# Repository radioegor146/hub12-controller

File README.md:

# hub12-controller

Simple HUB12 LED matrices USB controller using RP2040
Currently it is ready to use for 224x192 (7x12) 32x16 monochrome (red) matrices 
It uses:
- PIO to control 12 simultaneous SPI lanes
- DMA to push data to PIO
- Low-level USB w/o any libraries to push data to buffer

It achieves:
- ~160 FPS on 224x192 monochrome display with 12 parallel lanes

Pins are set in [this file](src/hub12.h)

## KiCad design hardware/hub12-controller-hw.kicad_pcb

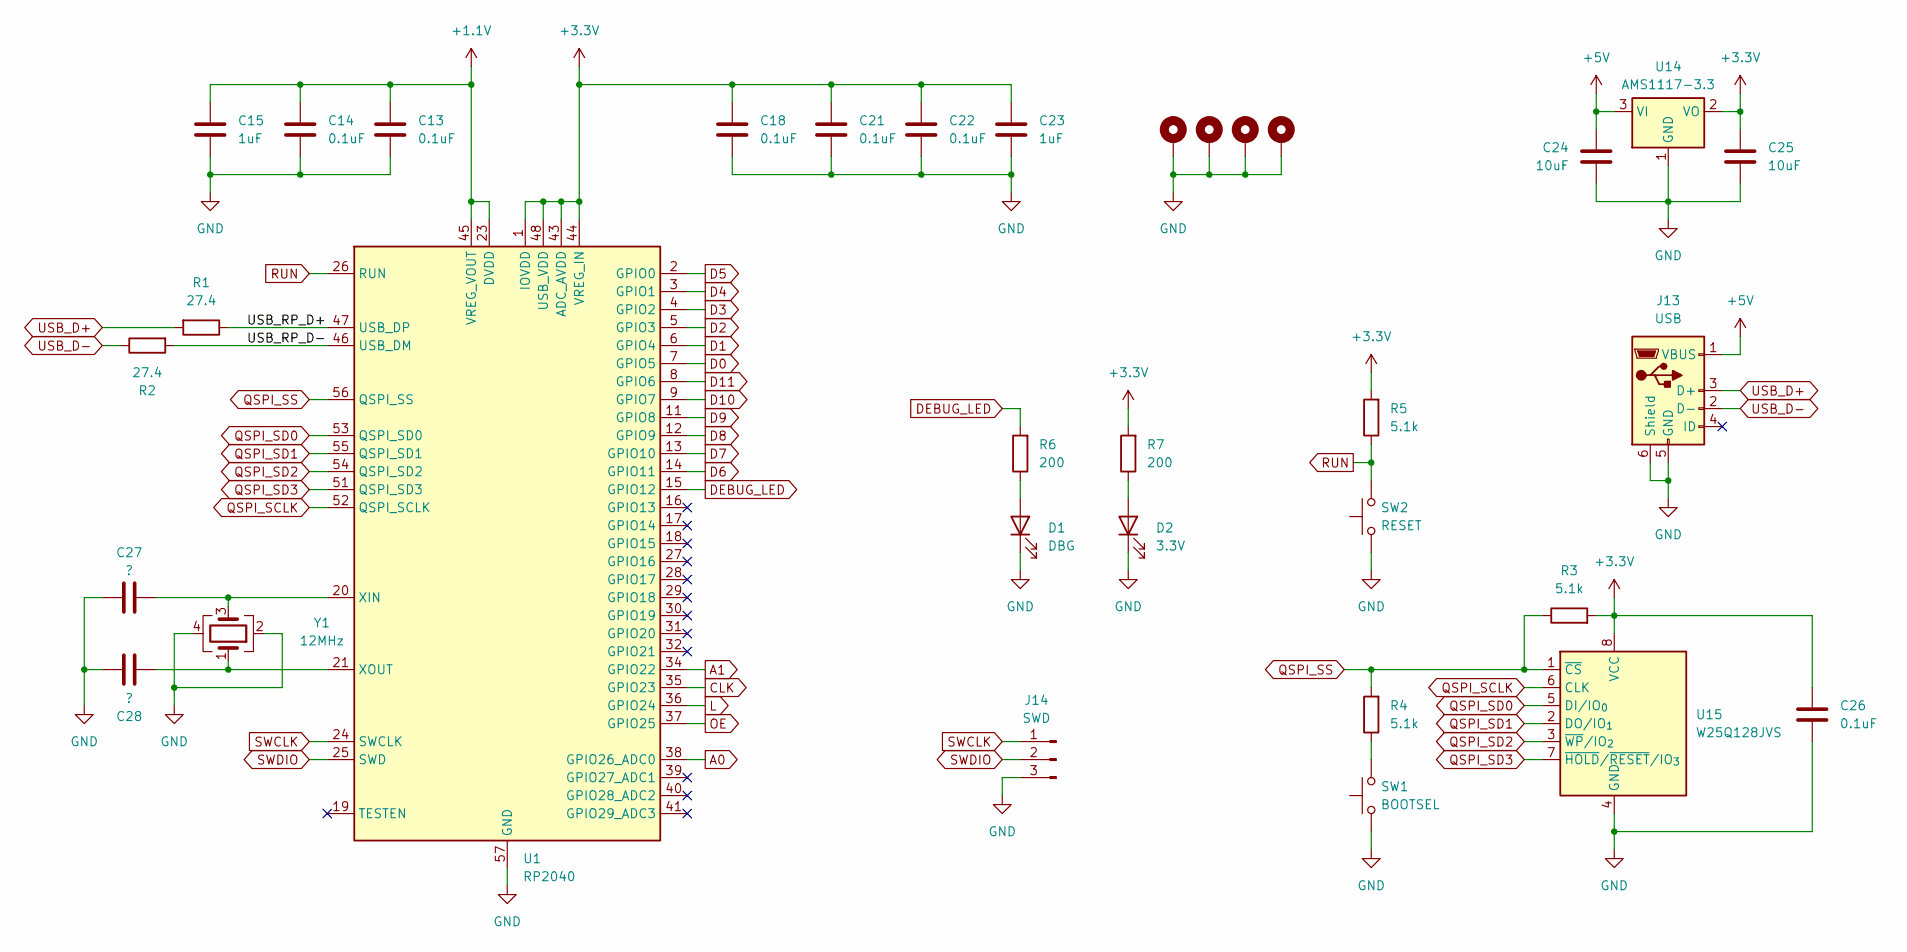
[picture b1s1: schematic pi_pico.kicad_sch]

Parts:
C13, C14, C18, C21, C22, C26: 0.1uF; C_0805_2012Metric
C15, C23: 1uF; C_0805_2012Metric
C24, C25: 10uF; C_0805_2012Metric
C27, C28: ?; C_0805_2012Metric
D1: DBG; LED_0805_2012Metric
D2: 3.3V; LED_0805_2012Metric
H1, H2, H3, H4: MountingHole_3.2mm_M3_DIN965_Pad_TopBottom
J13: USB; USB_Mini-B_Wuerth_65100516121_Horizontal
J14: SWD; PinHeader_1x03_P2.54mm_Vertical
R1, R2: 27.4; R_0805_2012Metric
R3, R4, R5: 5.1k; R_0805_2012Metric
R6, R7: 200; R_0805_2012Metric
SW1: BOOTSEL; SW_Push_SPST_NO_Alps_SKRK
SW2: RESET; SW_Push_SPST_NO_Alps_SKRK
U1: RP2040; QFN-56-1EP_7x7mm_P0.4mm_EP3.2x3.2mm
U14: AMS1117-3.3; SOT-223-3_TabPin2
U15: W25Q128JVS; SOIC-8_5.3x5.3mm_P1.27mm
Y1: 12MHz; Crystal_SMD_3225-4Pin_3.2x2.5mm_HandSoldering

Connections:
+1.1V: C13.1, C14.1, C15.1, U1.23 (DVDD), U1.45 (VREG_VOUT), U1.50 (DVDD)
+3.3V: C18.1, C21.1, C22.1, C23.1, C25.1, C26.1, R3.2, R5.2, R7.2, U1.1 (IOVDD), U1.10 (IOVDD), U1.22 (IOVDD), U1.33 (IOVDD), U1.42 (IOVDD), U1.43 (ADC_AVDD), U1.44 (VREG_IN), U1.48 (USB_VDD), U1.49 (IOVDD), U14.2 (VO), U15.8 (VCC); also elsewhere on the board
+5V: C24.1, J13.1 (VBUS), U14.3 (VI); also elsewhere on the board
/Pi Pico/USB_RP_D+: R1.1, U1.47 (USB_DP)
/Pi Pico/USB_RP_D-: R2.2, U1.46 (USB_DM)
A0: U1.38 (GPIO26_ADC0); also elsewhere on the board
A1: U1.34 (GPIO22); also elsewhere on the board
CLK: U1.35 (GPIO23); also elsewhere on the board
D0: U1.7 (GPIO5); also elsewhere on the board
D1: U1.6 (GPIO4); also elsewhere on the board
D2: U1.5 (GPIO3); also elsewhere on the board
D3: U1.4 (GPIO2); also elsewhere on the board
D4: U1.3 (GPIO1); also elsewhere on the board
D5: U1.2 (GPIO0); also elsewhere on the board
D6: U1.14 (GPIO11); also elsewhere on the board
D7: U1.13 (GPIO10); also elsewhere on the board
D8: U1.12 (GPIO9); also elsewhere on the board
D9: U1.11 (GPIO8); also elsewhere on the board
D10: U1.9 (GPIO7); also elsewhere on the board
D11: U1.8 (GPIO6); also elsewhere on the board
DEBUG_LED: R6.2, U1.15 (GPIO12)
GND: C13.2, C14.2, C15.2, C18.2, C21.2, C22.2, C23.2, C24.2, C25.2, C26.2, C27.1, C28.2, D1.1 (K), D2.1 (K), H1.1, H2.1, H3.1, H4.1, J13.5 (GND), J13.6 (Shield), J14.3, SW1.1, SW2.1, U1.57 (GND), U14.1 (GND), U15.4 (GND), Y1.2, Y1.4; also elsewhere on the board
L: U1.36 (GPIO24); also elsewhere on the board
unnamed: D1.2 (A), R6.1
unnamed: D2.2 (A), R7.1
unnamed: R4.1, SW1.2
unnamed: C27.2, U1.20 (XIN), Y1.3
unnamed: C28.1, U1.21 (XOUT), Y1.1
OE: U1.37 (GPIO25); also elsewhere on the board
QSPI_SCLK: U1.52 (QSPI_SCLK), U15.6 (CLK)
QSPI_SD0: U1.53 (QSPI_SD0), U15.5 (DI/IO_{0})
QSPI_SD1: U1.55 (QSPI_SD1), U15.2 (DO/IO_{1})
QSPI_SD2: U1.54 (QSPI_SD2), U15.3 (~WP/IO_{2})
QSPI_SD3: U1.51 (QSPI_SD3), U15.7 (~HOLD/~RESET/IO_{3})
QSPI_SS: R3.1, R4.2, U1.56 (QSPI_SS), U15.1 (~CS)
RUN: R5.1, SW2.2, U1.26 (RUN)
SWCLK: J14.1, U1.24 (SWCLK)
SWDIO: J14.2, U1.25 (SWD)
USB_D+: J13.3 (D+), R1.2
USB_D-: J13.2 (D-), R2.1

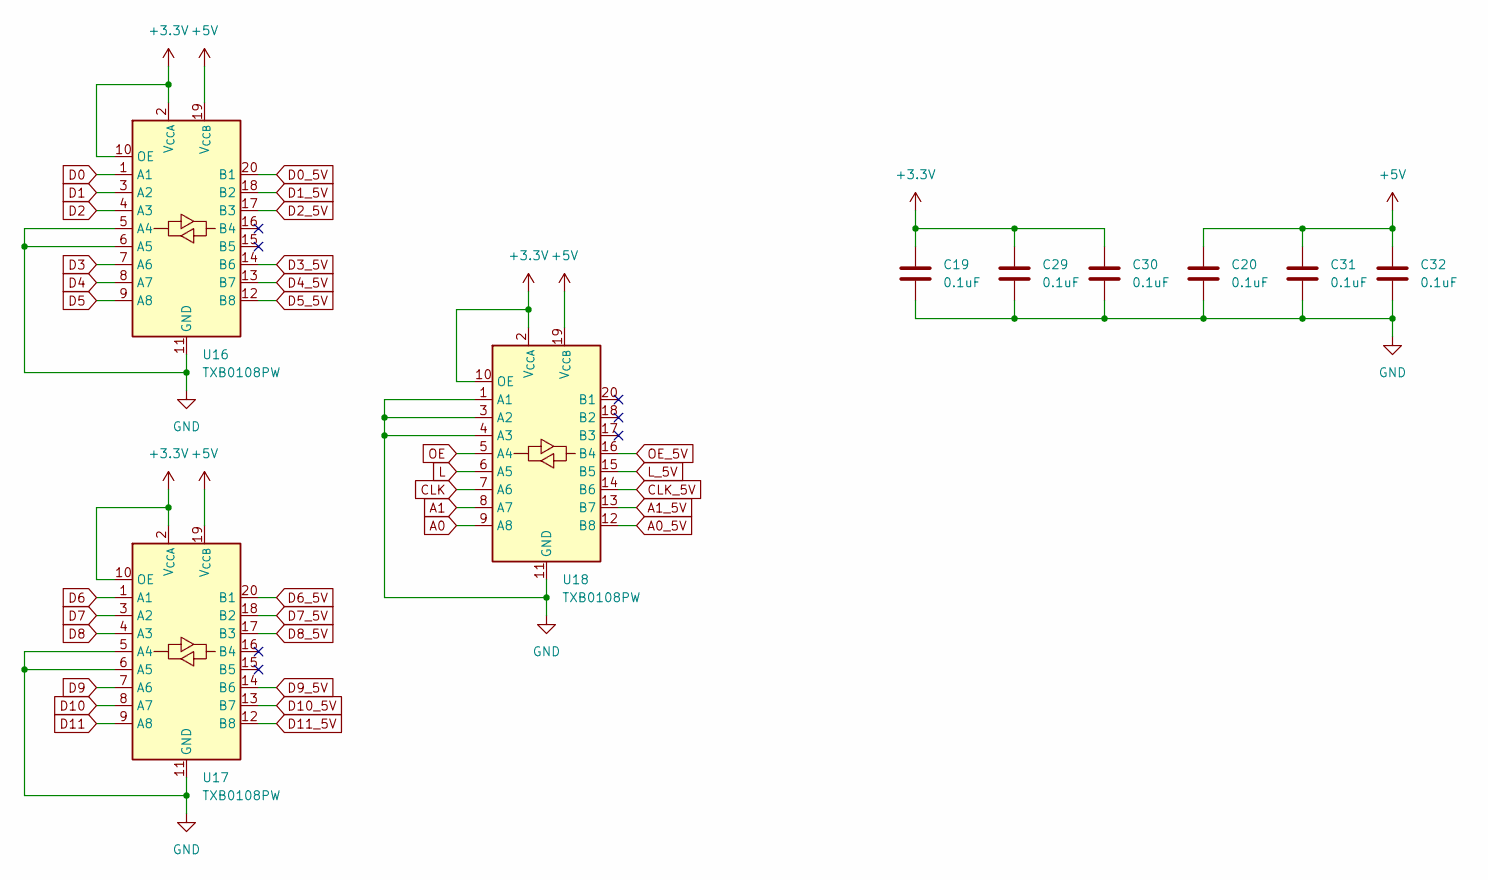
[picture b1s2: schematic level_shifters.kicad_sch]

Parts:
C19, C20, C29, C30, C31, C32: 0.1uF; C_0805_2012Metric
U16, U17, U18: TXB0108PW; TSSOP-20_4.4x6.5mm_P0.65mm

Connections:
+3.3V: C19.1, C29.1, C30.1, U16.2 (V_{CCA}), U16.10 (OE), U17.2 (V_{CCA}), U17.10 (OE), U18.2 (V_{CCA}), U18.10 (OE); also elsewhere on the board
+5V: C20.1, C31.1, C32.1, U16.19 (V_{CCB}), U17.19 (V_{CCB}), U18.19 (V_{CCB}); also elsewhere on the board
A0: U18.9 (A8); also elsewhere on the board
A0_5V: U18.12 (B8); also elsewhere on the board
A1: U18.8 (A7); also elsewhere on the board
A1_5V: U18.13 (B7); also elsewhere on the board
CLK: U18.7 (A6); also elsewhere on the board
CLK_5V: U18.14 (B6); also elsewhere on the board
D0: U16.1 (A1); also elsewhere on the board
D0_5V: U16.20 (B1); also elsewhere on the board
D1: U16.3 (A2); also elsewhere on the board
D1_5V: U16.18 (B2); also elsewhere on the board
D2: U16.4 (A3); also elsewhere on the board
D2_5V: U16.17 (B3); also elsewhere on the board
D3: U16.7 (A6); also elsewhere on the board
D3_5V: U16.14 (B6); also elsewhere on the board
D4: U16.8 (A7); also elsewhere on the board
D4_5V: U16.13 (B7); also elsewhere on the board
D5: U16.9 (A8); also elsewhere on the board
D5_5V: U16.12 (B8); also elsewhere on the board
D6: U17.1 (A1); also elsewhere on the board
D6_5V: U17.20 (B1); also elsewhere on the board
D7: U17.3 (A2); also elsewhere on the board
D7_5V: U17.18 (B2); also elsewhere on the board
D8: U17.4 (A3); also elsewhere on the board
D8_5V: U17.17 (B3); also elsewhere on the board
D9: U17.7 (A6); also elsewhere on the board
D9_5V: U17.14 (B6); also elsewhere on the board
D10: U17.8 (A7); also elsewhere on the board
D10_5V: U17.13 (B7); also elsewhere on the board
D11: U17.9 (A8); also elsewhere on the board
D11_5V: U17.12 (B8); also elsewhere on the board
GND: C19.2, C20.2, C29.2, C30.2, C31.2, C32.2, U16.5 (A4), U16.6 (A5), U16.11 (GND), U17.5 (A4), U17.6 (A5), U17.11 (GND), U18.1 (A1), U18.3 (A2), U18.4 (A3), U18.11 (GND); also elsewhere on the board
L: U18.6 (A5); also elsewhere on the board
L_5V: U18.15 (B5); also elsewhere on the board
OE: U18.5 (A4); also elsewhere on the board
OE_5V: U18.16 (B4); also elsewhere on the board

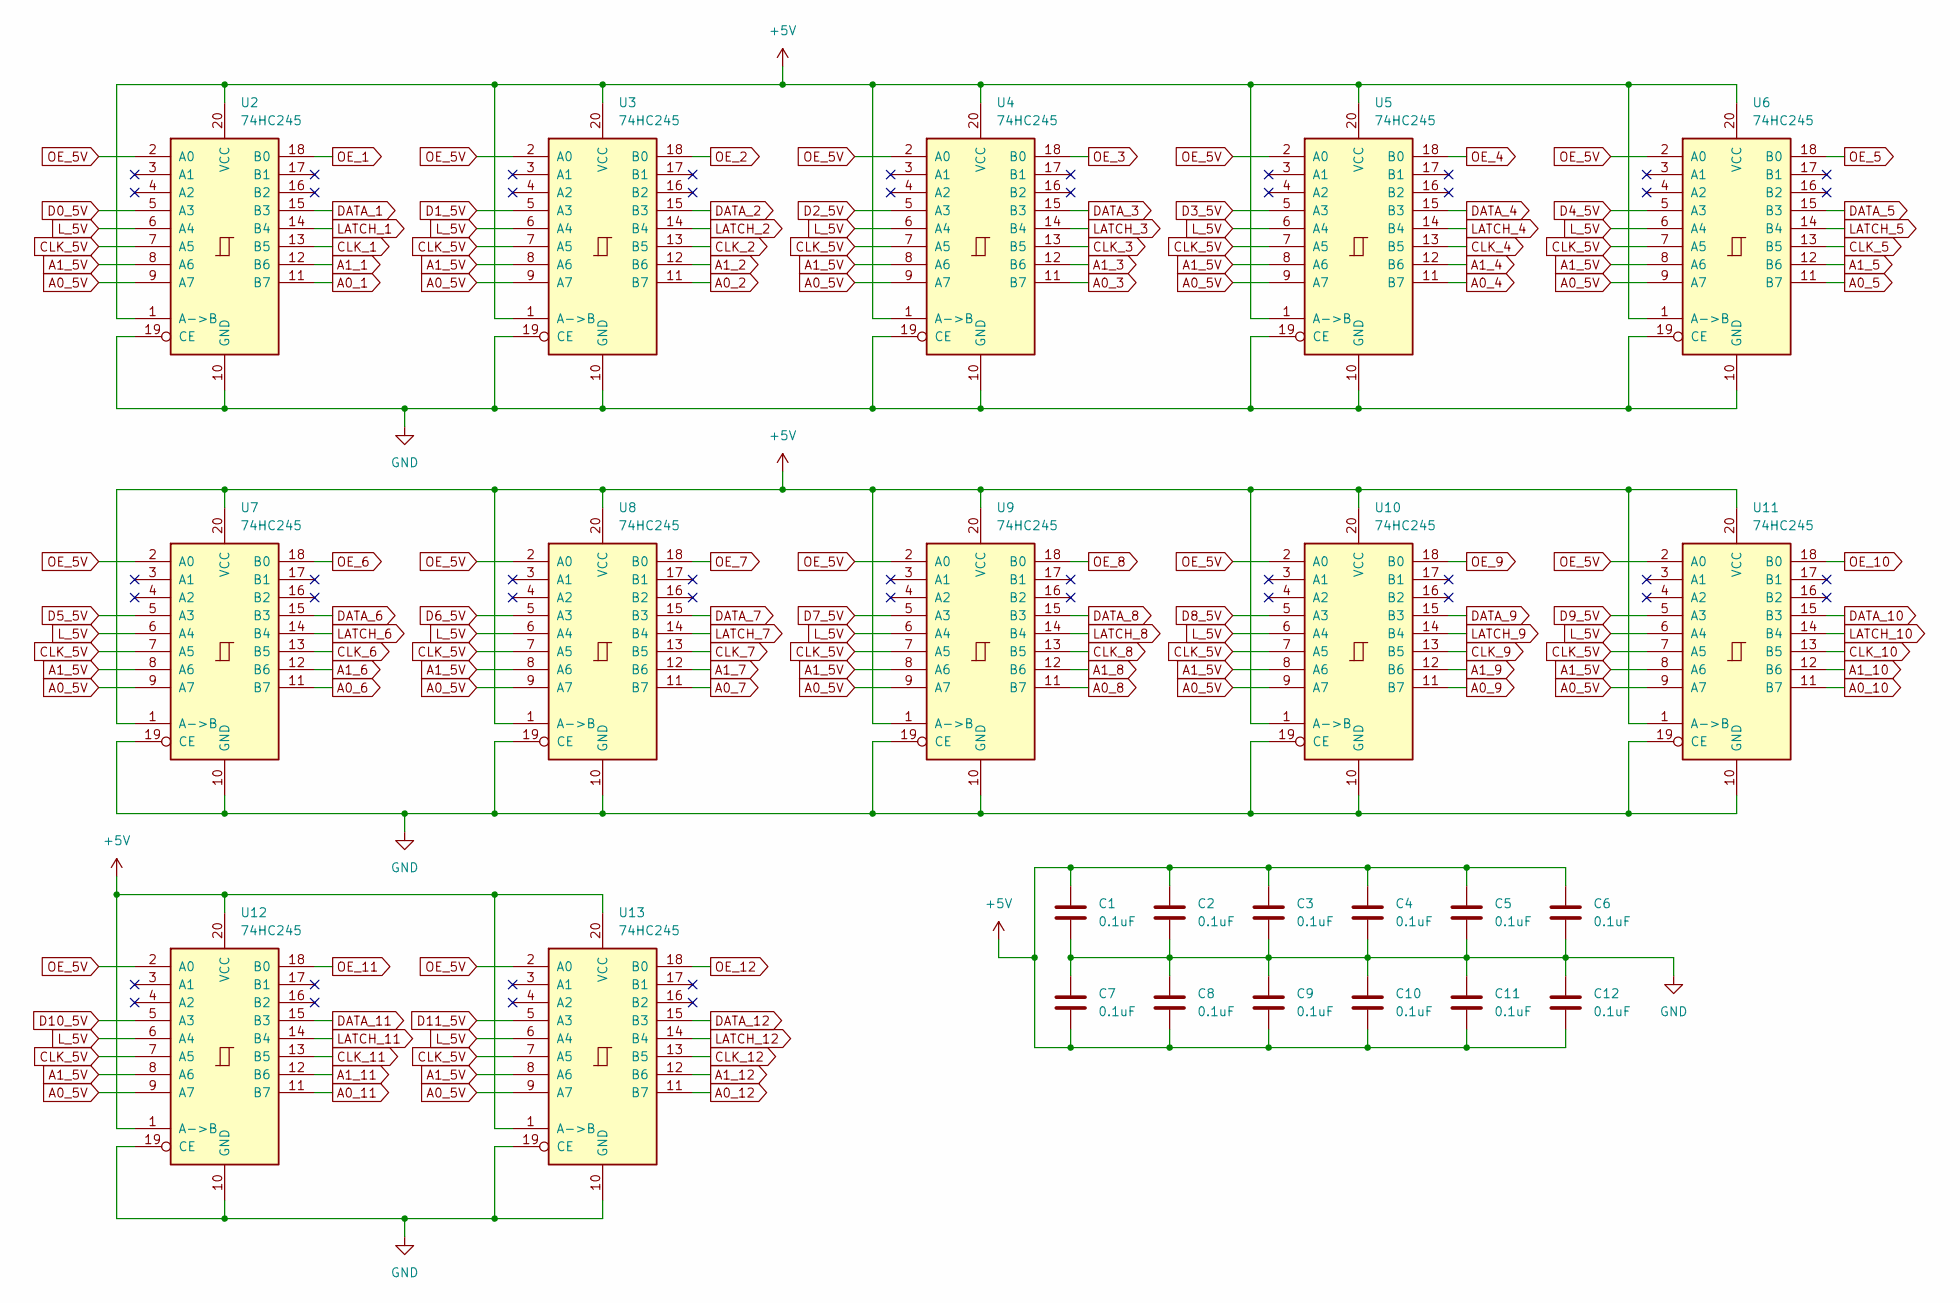
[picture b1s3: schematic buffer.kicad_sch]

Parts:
C1, C2, C3, C4, C5, C6, C7, C8, C9, C10, C11, C12: 0.1uF; C_0805_2012Metric
U2, U3, U4, U5, U6, U7, U8, U9, U10, U11, U12, U13: 74HC245; TSSOP-20_4.4x6.5mm_P0.65mm

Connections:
+5V: C1.1, C2.1, C3.1, C4.1, C5.1, C6.1, C7.2, C8.2, C9.2, C10.2, C11.2, C12.2, U2.1 (A->B), U2.20 (VCC), U3.1 (A->B), U3.20 (VCC), U4.1 (A->B), U4.20 (VCC), U5.1 (A->B), U5.20 (VCC), U6.1 (A->B), U6.20 (VCC), U7.1 (A->B), U7.20 (VCC), U8.1 (A->B), U8.20 (VCC), U9.1 (A->B), U9.20 (VCC), U10.1 (A->B), U10.20 (VCC), U11.1 (A->B), U11.20 (VCC), U12.1 (A->B), U12.20 (VCC), U13.1 (A->B), U13.20 (VCC); also elsewhere on the board
A0_1: U2.11 (B7); also elsewhere on the board
A0_2: U3.11 (B7); also elsewhere on the board
A0_3: U4.11 (B7); also elsewhere on the board
A0_4: U5.11 (B7); also elsewhere on the board
A0_5: U6.11 (B7); also elsewhere on the board
A0_5V: U2.9 (A7), U3.9 (A7), U4.9 (A7), U5.9 (A7), U6.9 (A7), U7.9 (A7), U8.9 (A7), U9.9 (A7), U10.9 (A7), U11.9 (A7), U12.9 (A7), U13.9 (A7); also elsewhere on the board
A0_6: U7.11 (B7); also elsewhere on the board
A0_7: U8.11 (B7); also elsewhere on the board
A0_8: U9.11 (B7); also elsewhere on the board
A0_9: U10.11 (B7); also elsewhere on the board
A0_10: U11.11 (B7); also elsewhere on the board
A0_11: U12.11 (B7); also elsewhere on the board
A0_12: U13.11 (B7); also elsewhere on the board
A1_1: U2.12 (B6); also elsewhere on the board
A1_2: U3.12 (B6); also elsewhere on the board
A1_3: U4.12 (B6); also elsewhere on the board
A1_4: U5.12 (B6); also elsewhere on the board
A1_5: U6.12 (B6); also elsewhere on the board
A1_5V: U2.8 (A6), U3.8 (A6), U4.8 (A6), U5.8 (A6), U6.8 (A6), U7.8 (A6), U8.8 (A6), U9.8 (A6), U10.8 (A6), U11.8 (A6), U12.8 (A6), U13.8 (A6); also elsewhere on the board
A1_6: U7.12 (B6); also elsewhere on the board
A1_7: U8.12 (B6); also elsewhere on the board
A1_8: U9.12 (B6); also elsewhere on the board
A1_9: U10.12 (B6); also elsewhere on the board
A1_10: U11.12 (B6); also elsewhere on the board
A1_11: U12.12 (B6); also elsewhere on the board
A1_12: U13.12 (B6); also elsewhere on the board
CLK_1: U2.13 (B5); also elsewhere on the board
CLK_2: U3.13 (B5); also elsewhere on the board
CLK_3: U4.13 (B5); also elsewhere on the board
CLK_4: U5.13 (B5); also elsewhere on the board
CLK_5: U6.13 (B5); also elsewhere on the board
CLK_5V: U2.7 (A5), U3.7 (A5), U4.7 (A5), U5.7 (A5), U6.7 (A5), U7.7 (A5), U8.7 (A5), U9.7 (A5), U10.7 (A5), U11.7 (A5), U12.7 (A5), U13.7 (A5); also elsewhere on the board
CLK_6: U7.13 (B5); also elsewhere on the board
CLK_7: U8.13 (B5); also elsewhere on the board
CLK_8: U9.13 (B5); also elsewhere on the board
CLK_9: U10.13 (B5); also elsewhere on the board
CLK_10: U11.13 (B5); also elsewhere on the board
CLK_11: U12.13 (B5); also elsewhere on the board
CLK_12: U13.13 (B5); also elsewhere on the board
D0_5V: U2.5 (A3); also elsewhere on the board
D1_5V: U3.5 (A3); also elsewhere on the board
D2_5V: U4.5 (A3); also elsewhere on the board
D3_5V: U5.5 (A3); also elsewhere on the board
D4_5V: U6.5 (A3); also elsewhere on the board
D5_5V: U7.5 (A3); also elsewhere on the board
D6_5V: U8.5 (A3); also elsewhere on the board
D7_5V: U9.5 (A3); also elsewhere on the board
D8_5V: U10.5 (A3); also elsewhere on the board
D9_5V: U11.5 (A3); also elsewhere on the board
D10_5V: U12.5 (A3); also elsewhere on the board
D11_5V: U13.5 (A3); also elsewhere on the board
DATA_1: U2.15 (B3); also elsewhere on the board
DATA_2: U3.15 (B3); also elsewhere on the board
DATA_3: U4.15 (B3); also elsewhere on the board
DATA_4: U5.15 (B3); also elsewhere on the board
DATA_5: U6.15 (B3); also elsewhere on the board
DATA_6: U7.15 (B3); also elsewhere on the board
DATA_7: U8.15 (B3); also elsewhere on the board
DATA_8: U9.15 (B3); also elsewhere on the board
DATA_9: U10.15 (B3); also elsewhere on the board
DATA_10: U11.15 (B3); also elsewhere on the board
DATA_11: U12.15 (B3); also elsewhere on the board
DATA_12: U13.15 (B3); also elsewhere on the board
GND: C1.2, C2.2, C3.2, C4.2, C5.2, C6.2, C7.1, C8.1, C9.1, C10.1, C11.1, C12.1, U2.10 (GND), U2.19 (CE), U3.10 (GND), U3.19 (CE), U4.10 (GND), U4.19 (CE), U5.10 (GND), U5.19 (CE), U6.10 (GND), U6.19 (CE), U7.10 (GND), U7.19 (CE), U8.10 (GND), U8.19 (CE), U9.10 (GND), U9.19 (CE), U10.10 (GND), U10.19 (CE), U11.10 (GND), U11.19 (CE), U12.10 (GND), U12.19 (CE), U13.10 (GND), U13.19 (CE); also elsewhere on the board
LATCH_1: U2.14 (B4); also elsewhere on the board
LATCH_2: U3.14 (B4); also elsewhere on the board
LATCH_3: U4.14 (B4); also elsewhere on the board
LATCH_4: U5.14 (B4); also elsewhere on the board
LATCH_5: U6.14 (B4); also elsewhere on the board
LATCH_6: U7.14 (B4); also elsewhere on the board
LATCH_7: U8.14 (B4); also elsewhere on the board
LATCH_8: U9.14 (B4); also elsewhere on the board
LATCH_9: U10.14 (B4); also elsewhere on the board
LATCH_10: U11.14 (B4); also elsewhere on the board
LATCH_11: U12.14 (B4); also elsewhere on the board
LATCH_12: U13.14 (B4); also elsewhere on the board
L_5V: U2.6 (A4), U3.6 (A4), U4.6 (A4), U5.6 (A4), U6.6 (A4), U7.6 (A4), U8.6 (A4), U9.6 (A4), U10.6 (A4), U11.6 (A4), U12.6 (A4), U13.6 (A4); also elsewhere on the board
OE_1: U2.18 (B0); also elsewhere on the board
OE_2: U3.18 (B0); also elsewhere on the board
OE_3: U4.18 (B0); also elsewhere on the board
OE_4: U5.18 (B0); also elsewhere on the board
OE_5: U6.18 (B0); also elsewhere on the board
OE_5V: U2.2 (A0), U3.2 (A0), U4.2 (A0), U5.2 (A0), U6.2 (A0), U7.2 (A0), U8.2 (A0), U9.2 (A0), U10.2 (A0), U11.2 (A0), U12.2 (A0), U13.2 (A0); also elsewhere on the board
OE_6: U7.18 (B0); also elsewhere on the board
OE_7: U8.18 (B0); also elsewhere on the board
OE_8: U9.18 (B0); also elsewhere on the board
OE_9: U10.18 (B0); also elsewhere on the board
OE_10: U11.18 (B0); also elsewhere on the board
OE_11: U12.18 (B0); also elsewhere on the board
OE_12: U13.18 (B0); also elsewhere on the board

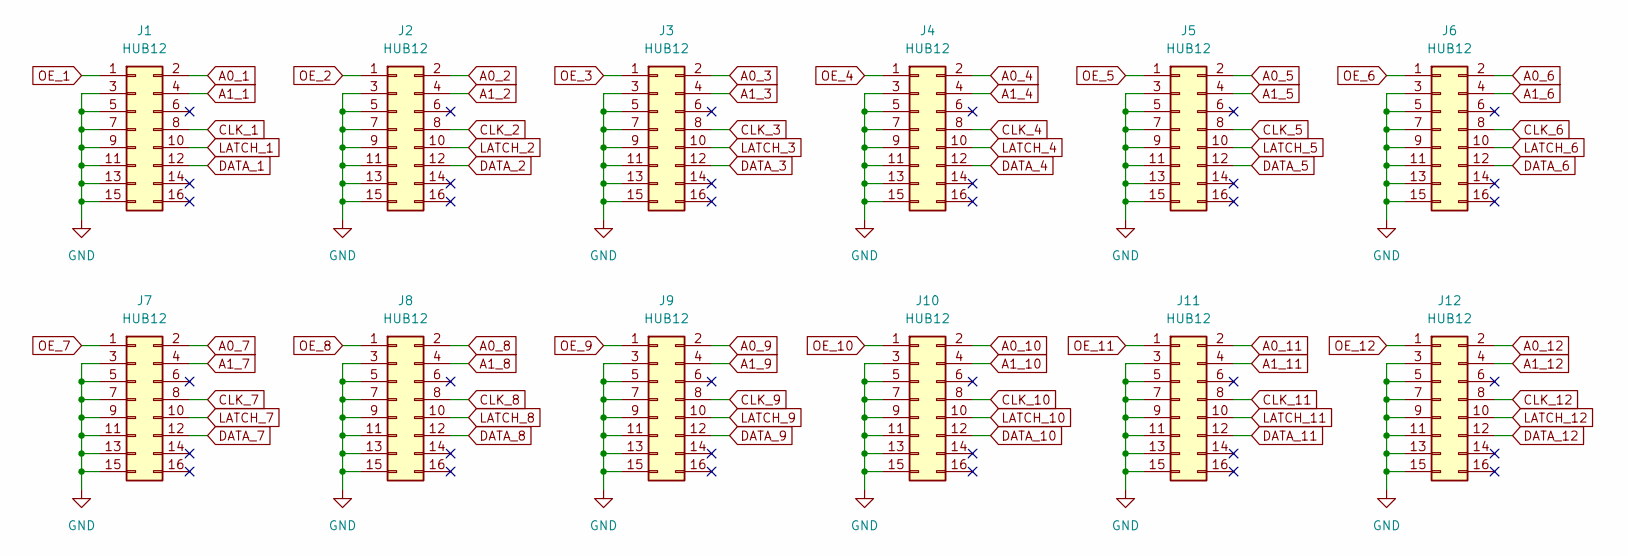
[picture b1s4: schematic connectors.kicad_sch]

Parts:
J1, J2, J3, J4, J5, J6, J7, J8, J9, J10, J11, J12: HUB12; IDC-Header_2x08_P2.54mm_Vertical

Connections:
A0_1: J1.2; also elsewhere on the board
A0_2: J2.2; also elsewhere on the board
A0_3: J3.2; also elsewhere on the board
A0_4: J4.2; also elsewhere on the board
A0_5: J5.2; also elsewhere on the board
A0_6: J6.2; also elsewhere on the board
A0_7: J7.2; also elsewhere on the board
A0_8: J8.2; also elsewhere on the board
A0_9: J9.2; also elsewhere on the board
A0_10: J10.2; also elsewhere on the board
A0_11: J11.2; also elsewhere on the board
A0_12: J12.2; also elsewhere on the board
A1_1: J1.4; also elsewhere on the board
A1_2: J2.4; also elsewhere on the board
A1_3: J3.4; also elsewhere on the board
A1_4: J4.4; also elsewhere on the board
A1_5: J5.4; also elsewhere on the board
A1_6: J6.4; also elsewhere on the board
A1_7: J7.4; also elsewhere on the board
A1_8: J8.4; also elsewhere on the board
A1_9: J9.4; also elsewhere on the board
A1_10: J10.4; also elsewhere on the board
A1_11: J11.4; also elsewhere on the board
A1_12: J12.4; also elsewhere on the board
CLK_1: J1.8; also elsewhere on the board
CLK_2: J2.8; also elsewhere on the board
CLK_3: J3.8; also elsewhere on the board
CLK_4: J4.8; also elsewhere on the board
CLK_5: J5.8; also elsewhere on the board
CLK_6: J6.8; also elsewhere on the board
CLK_7: J7.8; also elsewhere on the board
CLK_8: J8.8; also elsewhere on the board
CLK_9: J9.8; also elsewhere on the board
CLK_10: J10.8; also elsewhere on the board
CLK_11: J11.8; also elsewhere on the board
CLK_12: J12.8; also elsewhere on the board
DATA_1: J1.12; also elsewhere on the board
DATA_2: J2.12; also elsewhere on the board
DATA_3: J3.12; also elsewhere on the board
DATA_4: J4.12; also elsewhere on the board
DATA_5: J5.12; also elsewhere on the board
DATA_6: J6.12; also elsewhere on the board
DATA_7: J7.12; also elsewhere on the board
DATA_8: J8.12; also elsewhere on the board
DATA_9: J9.12; also elsewhere on the board
DATA_10: J10.12; also elsewhere on the board
DATA_11: J11.12; also elsewhere on the board
DATA_12: J12.12; also elsewhere on the board
GND: J1.3, J1.5, J1.7, J1.9, J1.11, J1.13, J1.15, J2.3, J2.5, J2.7, J2.9, J2.11, J2.13, J2.15, J3.3, J3.5, J3.7, J3.9, J3.11, J3.13, J3.15, J4.3, J4.5, J4.7, J4.9, J4.11, J4.13, J4.15, J5.3, J5.5, J5.7, J5.9, J5.11, J5.13, J5.15, J6.3, J6.5, J6.7, J6.9, J6.11, J6.13, J6.15, J7.3, J7.5, J7.7, J7.9, J7.11, J7.13, J7.15, J8.3, J8.5, J8.7, J8.9, J8.11, J8.13, J8.15, J9.3, J9.5, J9.7, J9.9, J9.11, J9.13, J9.15, J10.3, J10.5, J10.7, J10.9, J10.11, J10.13, J10.15, J11.3, J11.5, J11.7, J11.9, J11.11, J11.13, J11.15, J12.3, J12.5, J12.7, J12.9, J12.11, J12.13, J12.15; also elsewhere on the board
LATCH_1: J1.10; also elsewhere on the board
LATCH_2: J2.10; also elsewhere on the board
LATCH_3: J3.10; also elsewhere on the board
LATCH_4: J4.10; also elsewhere on the board
LATCH_5: J5.10; also elsewhere on the board
LATCH_6: J6.10; also elsewhere on the board
LATCH_7: J7.10; also elsewhere on the board
LATCH_8: J8.10; also elsewhere on the board
LATCH_9: J9.10; also elsewhere on the board
LATCH_10: J10.10; also elsewhere on the board
LATCH_11: J11.10; also elsewhere on the board
LATCH_12: J12.10; also elsewhere on the board
OE_1: J1.1; also elsewhere on the board
OE_2: J2.1; also elsewhere on the board
OE_3: J3.1; also elsewhere on the board
OE_4: J4.1; also elsewhere on the board
OE_5: J5.1; also elsewhere on the board
OE_6: J6.1; also elsewhere on the board
OE_7: J7.1; also elsewhere on the board
OE_8: J8.1; also elsewhere on the board
OE_9: J9.1; also elsewhere on the board
OE_10: J10.1; also elsewhere on the board
OE_11: J11.1; also elsewhere on the board
OE_12: J12.1; also elsewhere on the board

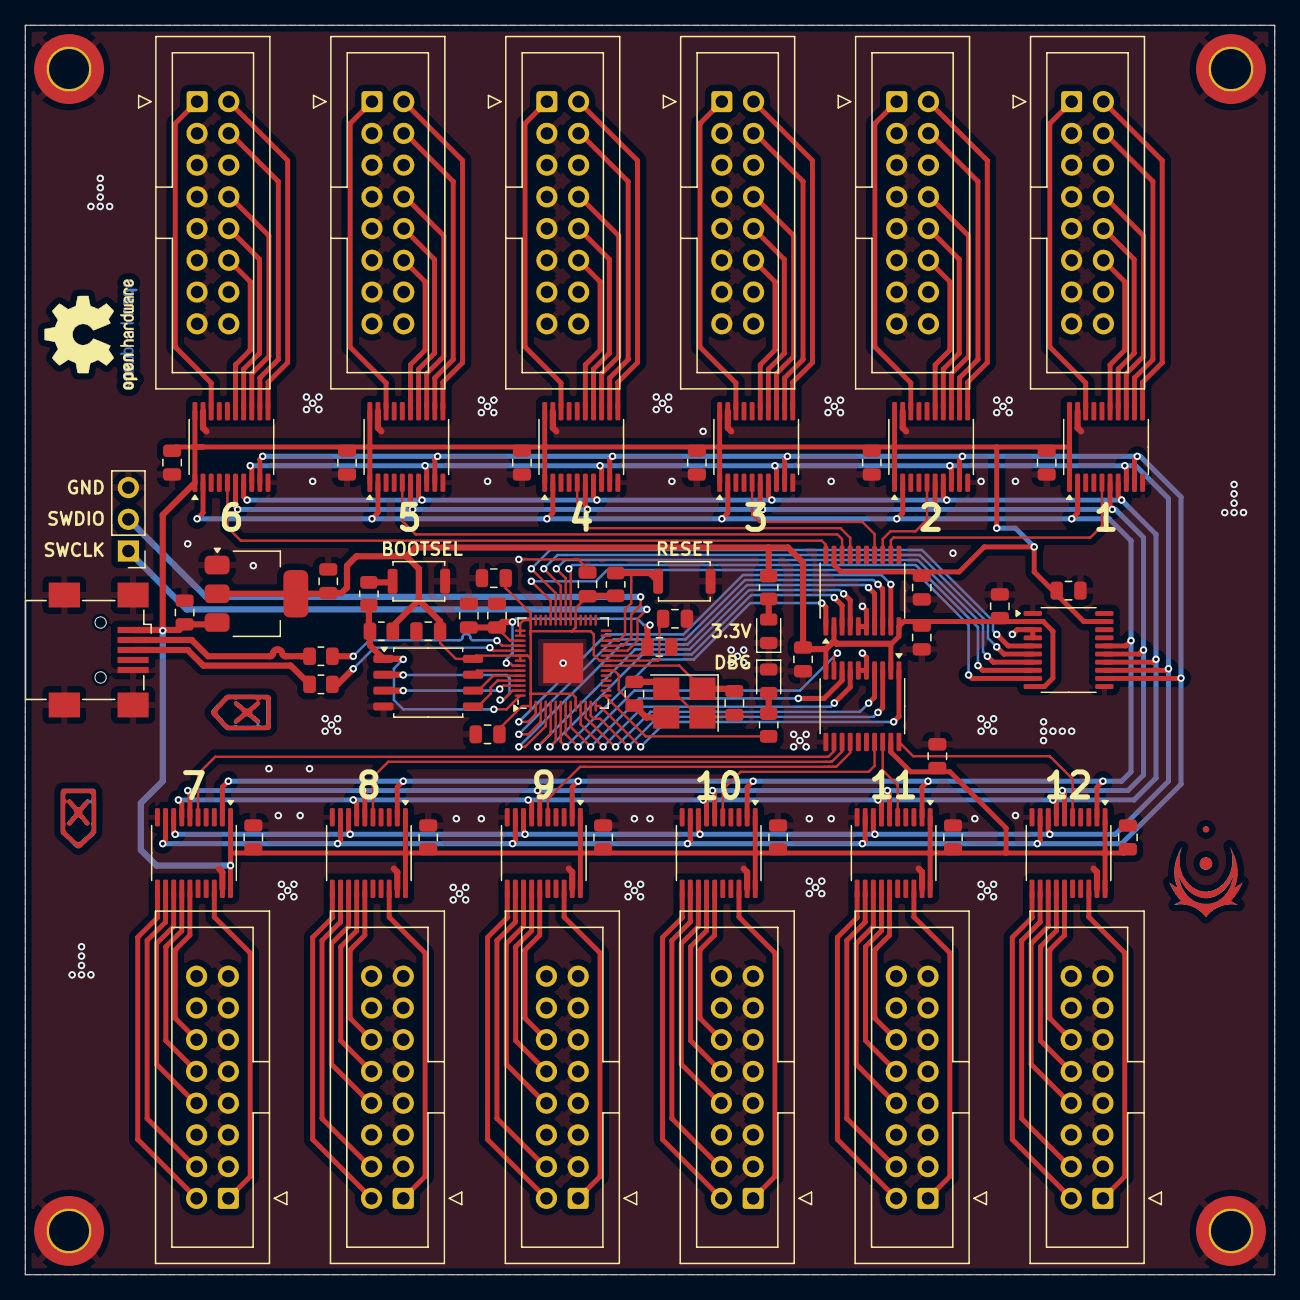
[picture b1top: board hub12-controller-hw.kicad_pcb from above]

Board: 2 copper layers, 100.0 x 100.0 mm, 78 parts (0 on the bottom side), 129 nets.

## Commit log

2025-09-01 main commit
2026-02-12 wut?
2026-02-12 add hardware and software
2026-03-17 chore: update
2026-03-18 fix dma buffer size
2026-03-19 move some stuff to debug
2026-03-19 add licenses
2026-03-19 change speed directive
2026-03-19 minor stuff
